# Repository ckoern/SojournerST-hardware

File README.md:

# SojournerST-hardware

KiCad project for the SojournerST two-channel closed-loop Motor Driver Board.
The firmware project can be found [here](https://github.com/ckoern/SojournerST).

The board is based on the TB6612 motor driver IC controlled via an STM32G441 (F4 should work as well) microcontroller and is designed to fit into a breadboard but also provides mounting holes to integrate it into a custom platform.

The controller uses quadrature encoder input to provide closed-loop PWM control to the driver IC. Power can either be supplied via USB to supply both logic and driver voltage or via a 3V3 logic and a motor voltage input (max. 15V).

Commanding can be done via UART or SPI.

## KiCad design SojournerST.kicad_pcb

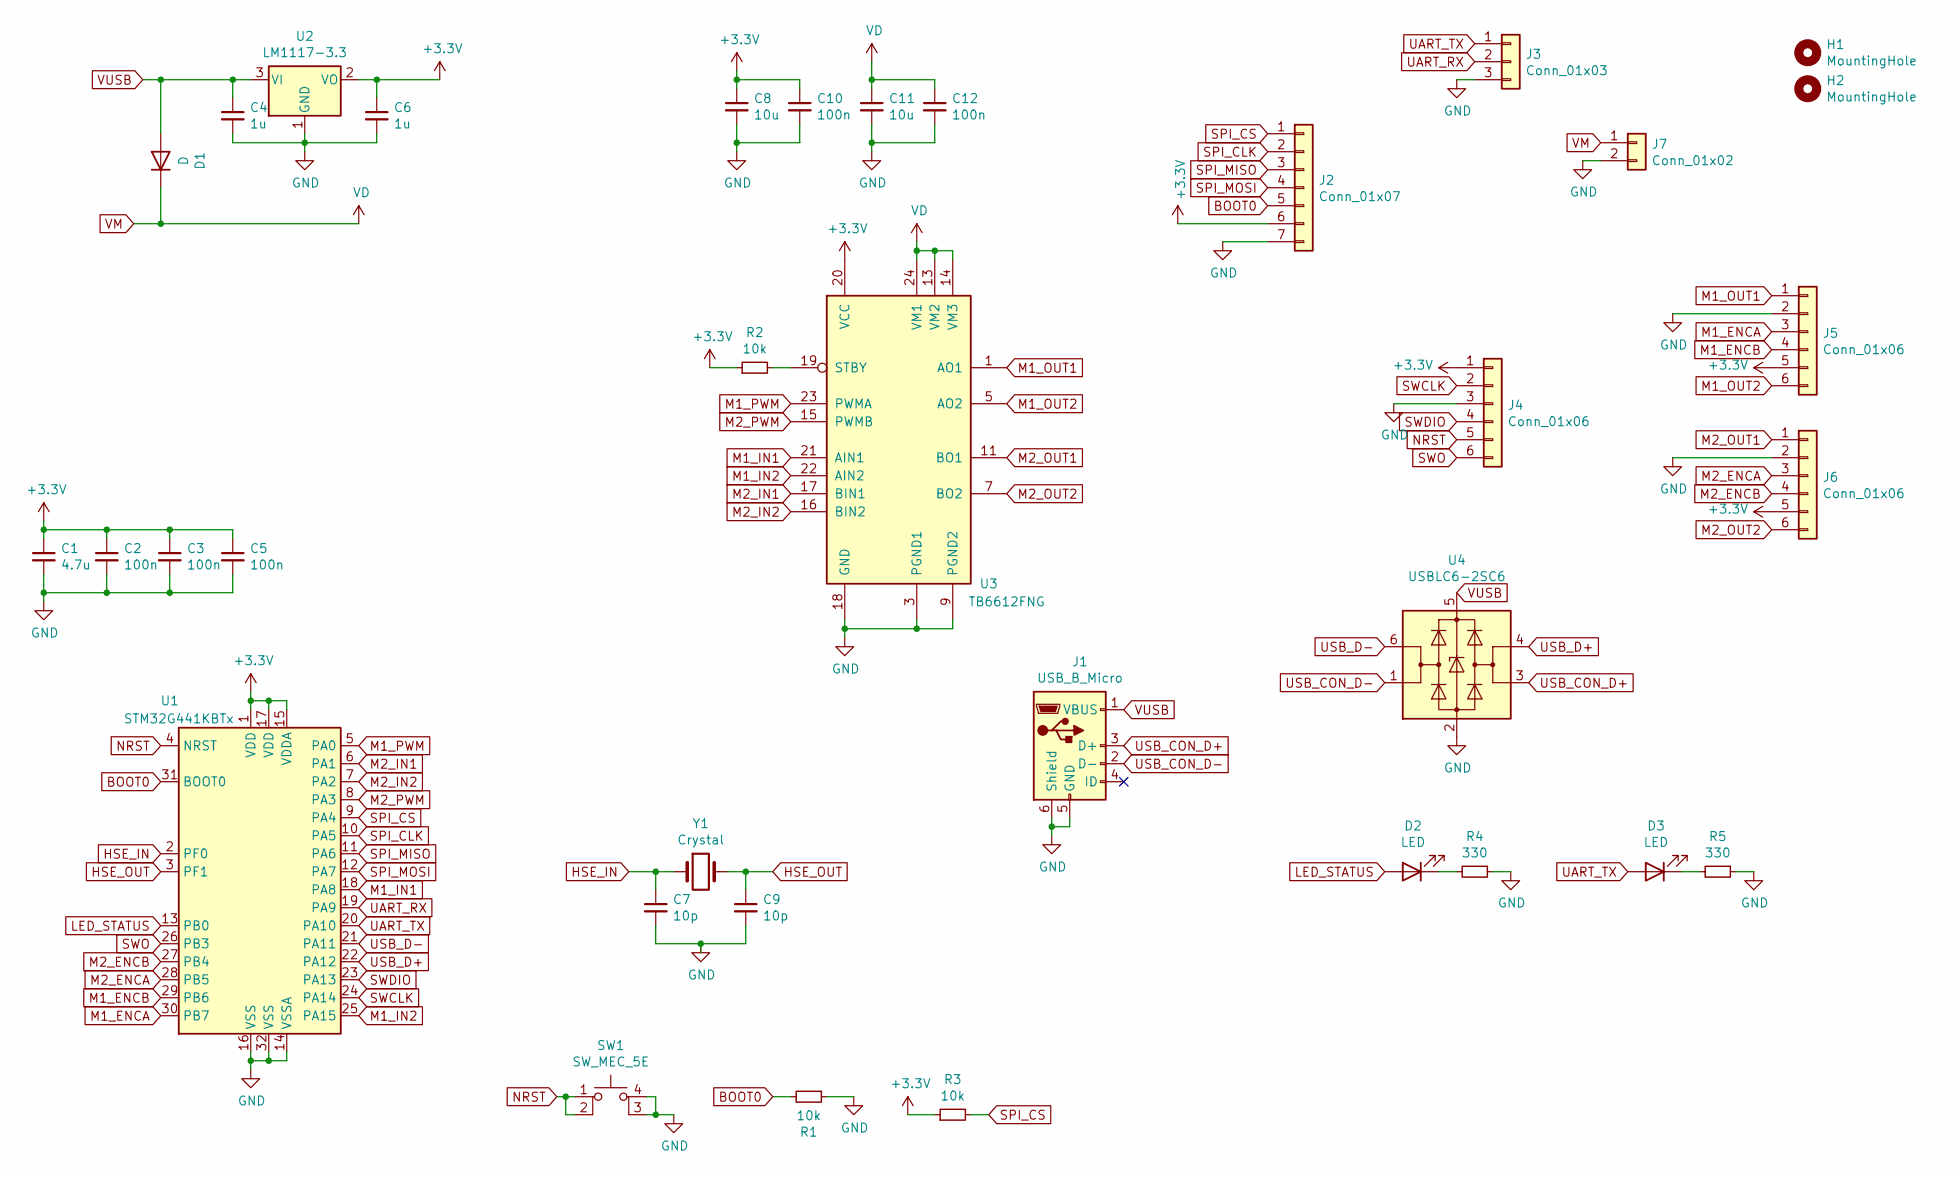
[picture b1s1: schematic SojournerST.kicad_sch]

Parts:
C1: 4.7u; C_0805_2012Metric
C2, C3, C5, C10, C12: 100n; C_0603_1608Metric
C4, C6: 1u; C_0805_2012Metric
C7, C9: 10p; C_0603_1608Metric
C8, C11: 10u; C_0805_2012Metric
D1: D; D_SMA
D2, D3: LED; LED_0603_1608Metric
H1, H2: MountingHole; MountingHole_2.2mm_M2_DIN965_Pad_TopOnly
J1: USB_B_Micro; USB_Micro-B_Amphenol_10118194_Horizontal
J2: Conn_01x07; PinHeader_1x07_P2.54mm_Vertical
J3: Conn_01x03; PinHeader_1x03_P2.54mm_Vertical
J4: Conn_01x06; PinHeader_2x03_P2.54mm_Vertical
J5, J6: Conn_01x06; PinHeader_1x06_P2.54mm_Vertical
J7: Conn_01x02; PinHeader_1x02_P2.54mm_Vertical
R1, R2, R3: 10k; R_0603_1608Metric
R4, R5: 330; R_0603_1608Metric
SW1: SW_MEC_5E; SW_SPST_Omron_B3FS-100xP
U1: STM32G441KBTx; LQFP-32_7x7mm_P0.8mm
U2: LM1117-3.3; SOT-23
U3: TB6612FNG; SSOP-24_5.3x8.2mm_P0.65mm
U4: USBLC6-2SC6; SOT-23-6
Y1: Crystal; Crystal_HC49-4H_Vertical

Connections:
+3V3: C1.1, C2.1, C3.1, C5.1, C6.1, C8.1, C10.1, J2.6, J4.1, J5.5, J6.5, R2.1, R3.1, U1.1 (VDD), U1.15 (VDDA), U1.17 (VDD), U2.2 (VO), U3.20 (VCC)
BOOT0: J2.5, R1.2, U1.31 (BOOT0)
GND: C1.2, C2.2, C3.2, C4.2, C5.2, C6.2, C7.2, C8.2, C9.2, C10.2, C11.2, C12.2, J1.5 (GND), J1.6 (Shield), J2.7, J3.3, J4.3, J5.2, J6.2, J7.2, R1.1, R4.1, R5.1, SW1.3 (K), SW1.4 (A), U1.14 (VSSA), U1.16 (VSS), U1.32 (VSS), U2.1 (GND), U3.3 (PGND1), U3.4 (PGND1), U3.9 (PGND2), U3.10 (PGND2), U3.18 (GND), U4.2 (GND)
HSE_IN: C7.1, U1.2 (PF0), Y1.1
HSE_OUT: C9.1, U1.3 (PF1), Y1.2
LED_STATUS: D2.2 (A), U1.13 (PB0)
M1_ENCA: J5.3, U1.30 (PB7)
M1_ENCB: J5.4, U1.29 (PB6)
M1_IN1: U1.18 (PA8), U3.21 (AIN1)
M1_IN2: U1.25 (PA15), U3.22 (AIN2)
M1_OUT1: J5.1, U3.1 (AO1), U3.2 (AO1)
M1_OUT2: J5.6, U3.5 (AO2), U3.6 (AO2)
M1_PWM: U1.5 (PA0), U3.23 (PWMA)
M2_ENCA: J6.3, U1.28 (PB5)
M2_ENCB: J6.4, U1.27 (PB4)
M2_IN1: U1.6 (PA1), U3.17 (BIN1)
M2_IN2: U1.7 (PA2), U3.16 (BIN2)
M2_OUT1: J6.1, U3.11 (BO1), U3.12 (BO1)
M2_OUT2: J6.6, U3.7 (BO2), U3.8 (BO2)
M2_PWM: U1.8 (PA3), U3.15 (PWMB)
NRST: J4.5, SW1.1, SW1.2, U1.4 (NRST)
unnamed: D2.1 (K), R4.2
unnamed: D3.1 (K), R5.2
unnamed: R2.2, U3.19 (STBY)
SPI_CLK: J2.2, U1.10 (PA5)
SPI_CS: J2.1, R3.2, U1.9 (PA4)
SPI_MISO: J2.3, U1.11 (PA6)
SPI_MOSI: J2.4, U1.12 (PA7)
SWCLK: J4.2, U1.24 (PA14)
SWDIO: J4.4, U1.23 (PA13)
SWO: J4.6, U1.26 (PB3)
UART_RX: J3.2, U1.19 (PA9)
UART_TX: D3.2 (A), J3.1, U1.20 (PA10)
USB_CON_D+: J1.3 (D+), U4.3 (I/O2)
USB_CON_D-: J1.2 (D-), U4.1 (I/O1)
USB_D+: U1.22 (PA12), U4.4 (I/O2)
USB_D-: U1.21 (PA11), U4.6 (I/O1)
VM: C11.1, C12.1, D1.1 (K), J7.1, U3.13 (VM2), U3.14 (VM3), U3.24 (VM1)
VUSB: C4.1, D1.2 (A), J1.1 (VBUS), U2.3 (VI), U4.5 (VBUS)

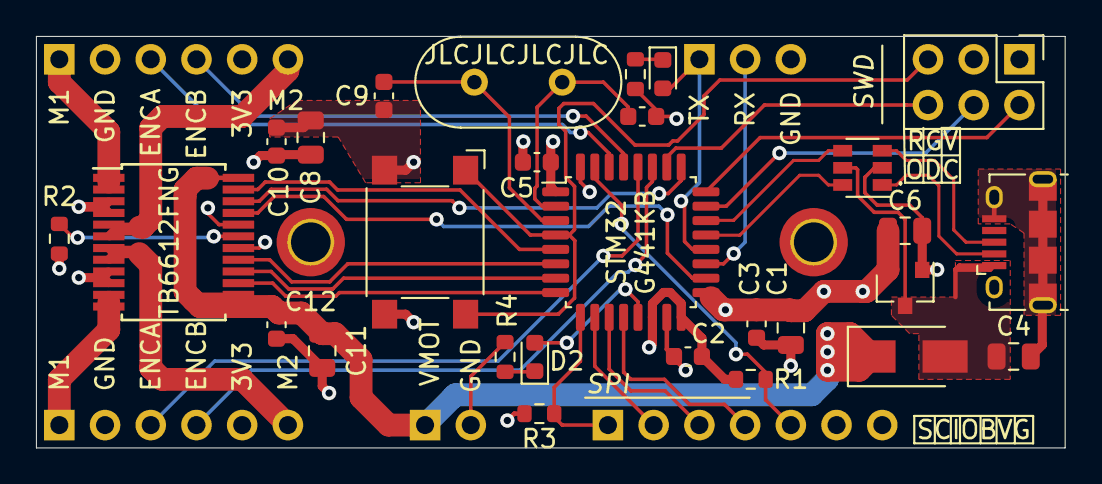
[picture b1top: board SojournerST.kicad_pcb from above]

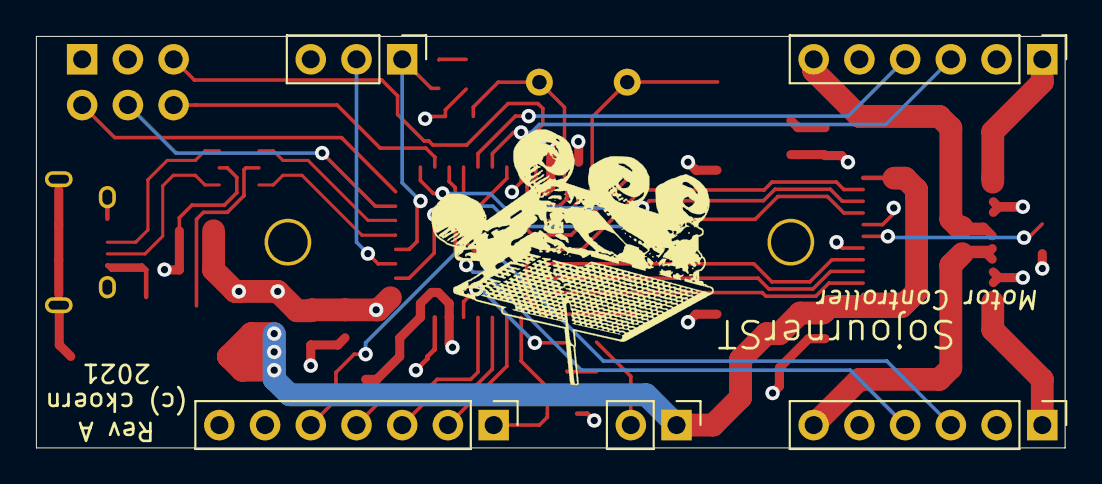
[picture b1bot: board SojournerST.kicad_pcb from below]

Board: 4 copper layers, 57.1 x 22.9 mm, 35 parts (5 on the bottom side), 39 nets.

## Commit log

2022-01-01 Inital commit containing the Rev A board files
2022-01-01 Create LICENSE
2022-01-01 Added a preview image
2022-01-01 Add image to repo
2022-01-01 Moved project into a subdirectory
2022-01-02 Added some details to the readme
